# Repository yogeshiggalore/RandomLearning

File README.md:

# RandomLearning
Random experiments and open source projects

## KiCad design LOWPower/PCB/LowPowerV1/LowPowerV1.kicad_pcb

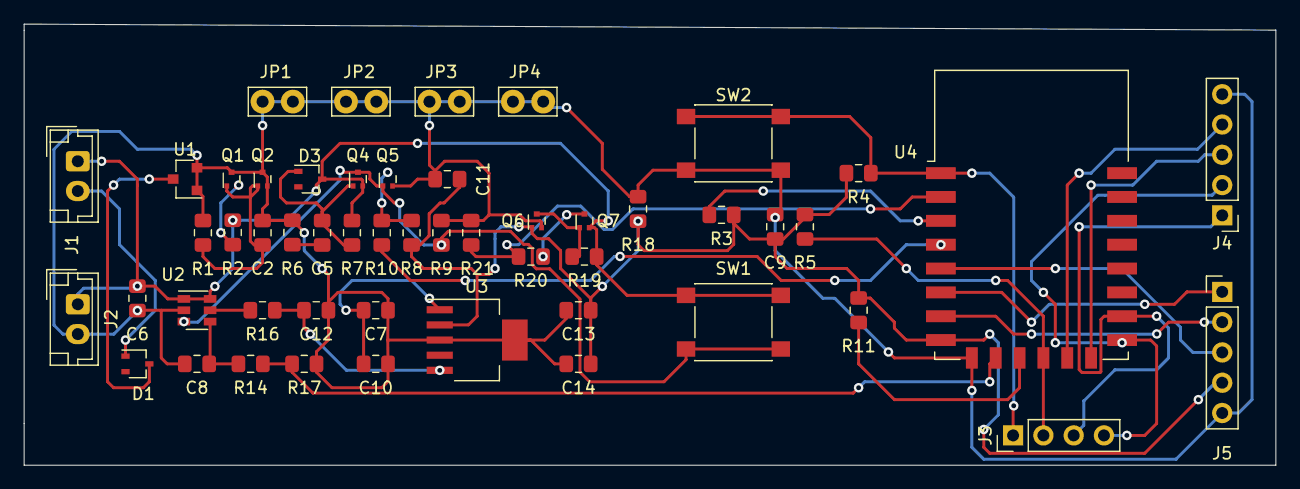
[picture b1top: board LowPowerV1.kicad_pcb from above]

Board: 2 copper layers, 105.0 x 37.0 mm, 52 parts (0 on the bottom side), 31 nets.

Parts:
C2: 100nf; C_0805_2012Metric_Pad1.15x1.40mm_HandSolder
C5, C8, C9, C10, C12, C14: 10u; C_0805_2012Metric_Pad1.15x1.40mm_HandSolder
C6, C7, C11, C13: 100n; C_0805_2012Metric_Pad1.15x1.40mm_HandSolder
D1, D3: BAT54W; SOT-323_SC-70
J1: CN1; JST_EH_B2B-EH-A_1x02_P2.50mm_Vertical
J2: BatInput; JST_EH_B2B-EH-A_1x02_P2.50mm_Vertical
J3: Prog; PinHeader_1x04_P2.54mm_Vertical
J4: CONN-1; PinHeader_1x05_P2.54mm_Vertical
J5: CONN-2; PinHeader_1x05_P2.54mm_Vertical
JP1, JP2, JP3, JP4: TP; TestPoint_Bridge_Pitch2.54mm_Drill1.0mm
Q1, Q4, Q7: RZM001P02T2L; SOT-723
Q2, Q5, Q6: RUM001L02T2CL; SOT-723
R1, R3, R4, R5, R8, R11, R14, R16, R17, R18, R19, R21: 10K; R_0805_2012Metric_Pad1.15x1.40mm_HandSolder
R2, R6: 100; R_0805_2012Metric_Pad1.15x1.40mm_HandSolder
R7: 100K; R_0805_2012Metric_Pad1.15x1.40mm_HandSolder
R9: 124K; R_0805_2012Metric_Pad1.15x1.40mm_HandSolder
R10: 1K; R_0805_2012Metric_Pad1.15x1.40mm_HandSolder
R20: 49.9K; R_0805_2012Metric_Pad1.15x1.40mm_HandSolder
SW1, SW2: SW; SW_Push_1P1T_NO_6x6mm_H9.5mm
U1: TPS3839DBZ; SOT-23
U2: TPL5111; SOT-23-6
U3: TPS73733DCQ; SOT-223-6
U4: ESP-12E

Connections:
+3V3: C9.1, C11.1, C13.1, C14.1, J5.4, Q6.1, R3.1, R4.1, R5.1, R8.2, R11.2, R18.2, U3.2, U4.8
/BAT_DIV: R20.1, R21.2, U4.2
/DELAY: Q4.3, Q5.1, R9.2, SW1.1, U2.3
/DONE: R14.1, R17.1, U4.10
/DRIVE: C12.1, R16.1, U3.5
/DTR: J3.2, R5.2, U4.12
/DTX: R11.1, U4.11
/EXT_WAKE: R10.1, U4.4
/I2C_SCL: J4.3, U4.14
/I2C_SDA: J4.4, U4.13
/RST: J3.1, R4.2, SW2.1, U4.1
/RX: J3.4, J4.2, U4.15
/SPI_MISO: J5.1, U4.6
/SPI_MOSI: J5.2, U4.7
/SPI_SCK: J5.3, U4.5
/TX: J3.3, J4.1, U4.16
/VBAT: C6.1, D3.3, J1.1, J2.1, Q4.2, Q7.2, R2.1, R7.2, R19.2, SW1.2, U2.1, U2.6
GND: C2.2, C6.2, C7.2, C8.2, C9.2, C10.2, C11.2, C12.2, C13.2, C14.2, J2.2, J4.5, J5.5, JP1.1, JP2.1, JP3.1, JP4.1, Q1.3, Q2.2, Q2.3, Q5.2, Q6.2, R1.2, R6.2, R9.1, R17.2, R18.1, R21.1, SW2.2, U1.1, U1.2, U2.2, U3.3, U3.6, U4.9
unnamed: C2.1, Q1.1, Q2.1, R1.1
unnamed: C5.1, D3.1, Q4.1, R7.1
unnamed: C5.2, R6.1
unnamed: C8.1, R14.2, U2.4
unnamed: C7.1, C10.1, U3.1
unnamed: D1.1, J1.2
unnamed: D1.3, U1.3
unnamed: Q1.2, R2.2
unnamed: Q5.3, R8.1, R10.2
unnamed: Q6.3, Q7.1, R19.1
unnamed: Q7.3, R20.2
unnamed: R3.2, U4.3
unnamed: R16.2, U2.5

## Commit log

2020-11-02 First commit
    includes
    1. MQTT demo and documents
    2. Alexa demo and documents
    3. IOT product development
2021-03-19 19-03-2021
    Regular commit
2021-03-19 test1
    test1
2021-03-19 test2
    df;jds
2021-03-19 test3
    df;lksd;fk
2021-03-19 test4
    dfklsdf
2021-03-19 test56
    ds;kad;laks;dk
2021-03-19 test34
    bgfdghdfg
2021-03-19 test3456
    fhgdh
2021-03-19 test78
    dfvdsfsd
2021-03-19 test123
    sdgfsdfg
2021-03-19 test678
    dfdf
2021-04-30 30-04-2021
    30-04-2021 commit
